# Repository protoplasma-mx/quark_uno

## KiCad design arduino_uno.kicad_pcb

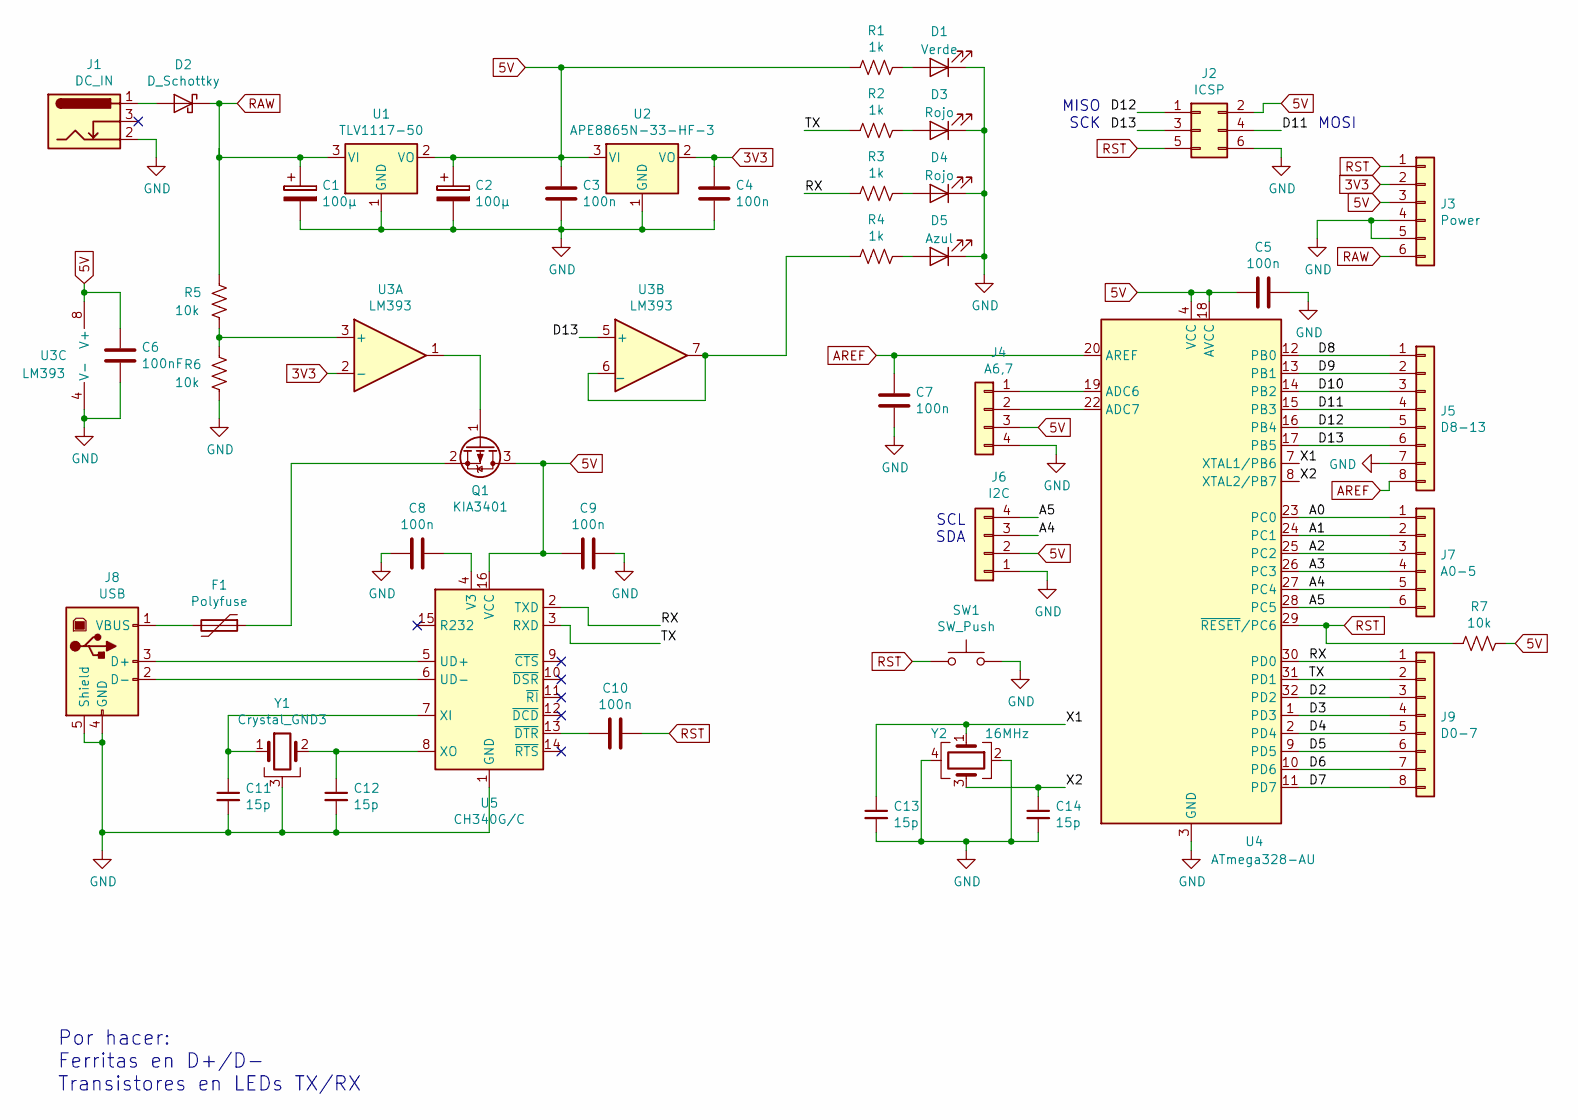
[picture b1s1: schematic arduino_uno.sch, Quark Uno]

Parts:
C1, C2: 100µ; CP_Elec_6.3x5.4
C3, C4, C5, C7, C8, C9, C10: 100n; C_0603_1608Metric
C6: 100nF; C_0603_1608Metric
C11, C12, C13, C14: 15p; C_0603_1608Metric
D1: Verde; LED_0603_1608Metric
D2: D_Schottky; D_SMA
D3, D4: Rojo; LED_0603_1608Metric
D5: Azul; LED_0603_1608Metric
F1: Polyfuse; Fuse_1206_3216Metric
J1: DC_IN; BarrelJack_Horizontal
J2: ICSP; PinHeader_2x03_P2.54mm_Vertical
J3: Power; PinSocket_1x06_P2.54mm_Vertical
J4: A6,7; PinSocket_1x04_P2.54mm_Vertical
J5: D8-13; PinSocket_1x08_P2.54mm_Vertical
J6: I2C; PinSocket_1x04_P2.54mm_Vertical
J7: A0-5; PinSocket_1x06_P2.54mm_Vertical
J8: USB; USB_B_OST_USB-B1HSxx_Horizontal
J9: D0-7; PinSocket_1x08_P2.54mm_Vertical
Q1: KIA3401; SOT-23
R1, R2, R3, R4: 1k; R_0603_1608Metric
R5, R6, R7: 10k; R_0603_1608Metric
SW1: SW_Push; Switch_SMD_4545
U1: TLV1117-50; SOT-223-3_TabPin2
U2: APE8865N-33-HF-3; SOT-23
U3: LM393; SOIC-8_3.9x4.9mm_P1.27mm
U4: ATmega328-AU; TQFP-32_7x7mm_P0.8mm
U5: CH340G/C; SOP-16_4.4x10.4mm_P1.27mm
Y1: Crystal_GND3; Crystal_DS26_D2.0mm_L6.0mm_Horizontal_Grounded
Y2: 16MHz; Crystal_SMD_SeikoEpson_TSX3225-4Pin_3.2x2.5mm

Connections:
3V3: C4.1, J3.2, U2.2 (VO), U3.2 (-)
5V: C2.1, C3.1, C5.2, C6.1, C9.2, J2.2, J3.3, J4.3, J6.2, Q1.3 (D), R1.2, R7.1, U1.2 (VO), U2.3 (VI), U3.8 (V+), U4.4 (VCC), U4.6 (VCC), U4.18 (AVCC), U5.16 (VCC)
/A0: J7.1, U4.23 (PC0)
/A1: J7.2, U4.24 (PC1)
/A2: J7.3, U4.25 (PC2)
/A3: J7.4, U4.26 (PC3)
/A4: J6.3, J7.5, U4.27 (PC4)
/A5: J6.4, J7.6, U4.28 (PC5)
/D2: J9.3, U4.32 (PD2)
/D3: J9.4, U4.1 (PD3)
/D4: J9.5, U4.2 (PD4)
/D5: J9.6, U4.9 (PD5)
/D6: J9.7, U4.10 (PD6)
/D7: J9.8, U4.11 (PD7)
/D8: J5.1, U4.12 (PB0)
/D9: J5.2, U4.13 (PB1)
/D10: J5.3, U4.14 (PB2)
/D11: J2.4, J5.4, U4.15 (PB3)
/D12: J2.1, J5.5, U4.16 (PB4)
/D13: J2.3, J5.6, U3.5 (+), U4.17 (PB5)
/RX: J9.1, R3.2, U4.30 (PD0), U5.2 (TXD)
/TX: J9.2, R2.2, U4.31 (PD1), U5.3 (RXD)
/X1: C13.1, U4.7 (XTAL1/PB6), Y2.1
/X2: C14.1, U4.8 (XTAL2/PB7), Y2.3
AREF: C7.1, J5.8, U4.20 (AREF)
GND: C1.2, C2.2, C3.2, C4.2, C5.1, C6.2, C7.2, C8.2, C9.1, C11.2, C12.2, C13.2, C14.2, D1.1 (K), D3.1 (K), D4.1 (K), D5.1 (K), J1.2, J2.6, J3.4, J3.5, J4.4, J5.7, J6.1, J8.4 (GND), J8.5 (Shield), R6.1, SW1.2, U1.1 (GND), U2.1 (GND), U3.4 (V-), U4.3 (GND), U4.5 (GND), U4.21 (GND), U5.1 (GND), Y1.3, Y2.2, Y2.4
unnamed: C8.1, U5.4 (V3)
unnamed: C10.2, U5.13 (~DTR)
unnamed: C11.1, U5.7 (XI), Y1.1
unnamed: C12.1, U5.8 (XO), Y1.2
unnamed: D1.2 (A), R1.1
unnamed: D2.2 (A), J1.1
unnamed: D3.2 (A), R2.1
unnamed: D4.2 (A), R3.1
unnamed: D5.2 (A), R4.1
unnamed: F1.1, Q1.2 (S)
unnamed: F1.2, J8.1 (VBUS)
unnamed: J4.1, U4.19 (ADC6)
unnamed: J4.2, U4.22 (ADC7)
unnamed: J8.2 (D-), U5.6 (UD-)
unnamed: J8.3 (D+), U5.5 (UD+)
unnamed: Q1.1 (G), U3.1
unnamed: R4.2, U3.6 (_), U3.7
unnamed: R5.1, R6.2, U3.3 (+)
RAW: C1.1, D2.1 (K), J3.6, R5.2, U1.3 (VI)
RST: C10.1, J2.5, J3.1, R7.2, SW1.1, U4.29 (~RESET~/PC6)

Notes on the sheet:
Por hacer: Ferritas en D+/D- Transistores en LEDs TX/RX
SCL SDA
MISO SCK
MOSI

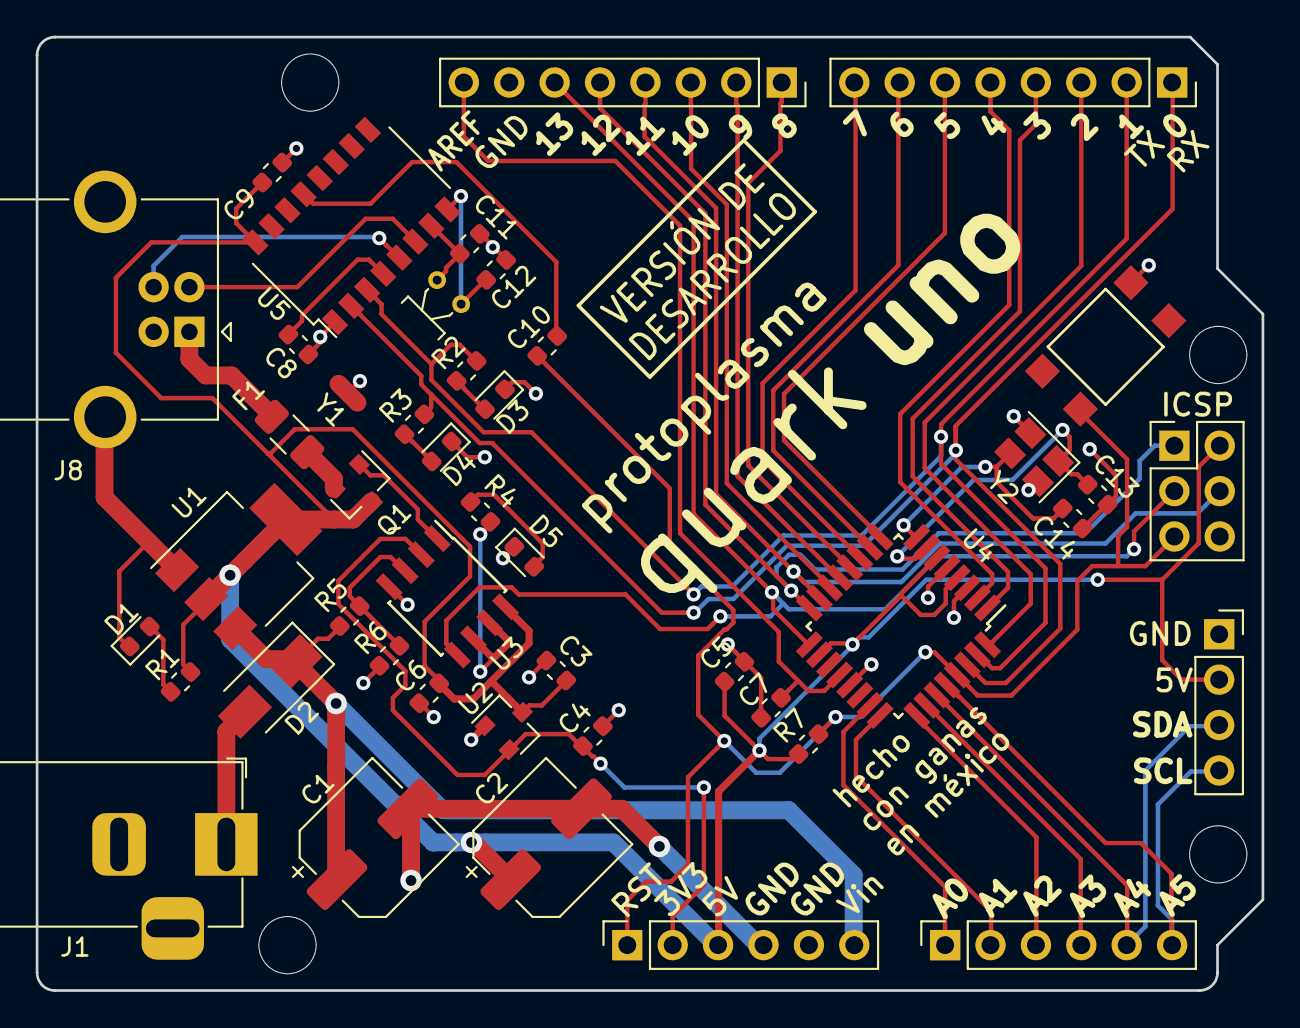
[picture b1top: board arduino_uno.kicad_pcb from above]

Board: 2 copper layers, 68.6 x 53.3 mm, 48 parts (0 on the bottom side), 44 nets.

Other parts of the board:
@HOLE0, @HOLE1, @HOLE2, @HOLE3: (no value)

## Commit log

2019-07-17 Commit inicial, diagrama completo
2019-07-17 Se agrega to-do, mejoras esteticas para legibilidad
2019-07-18 Se agregan ICSP e I2C, varias mejoras para legibilidad
2019-07-22 Primera revision completa, se fabrica para evaluacion
